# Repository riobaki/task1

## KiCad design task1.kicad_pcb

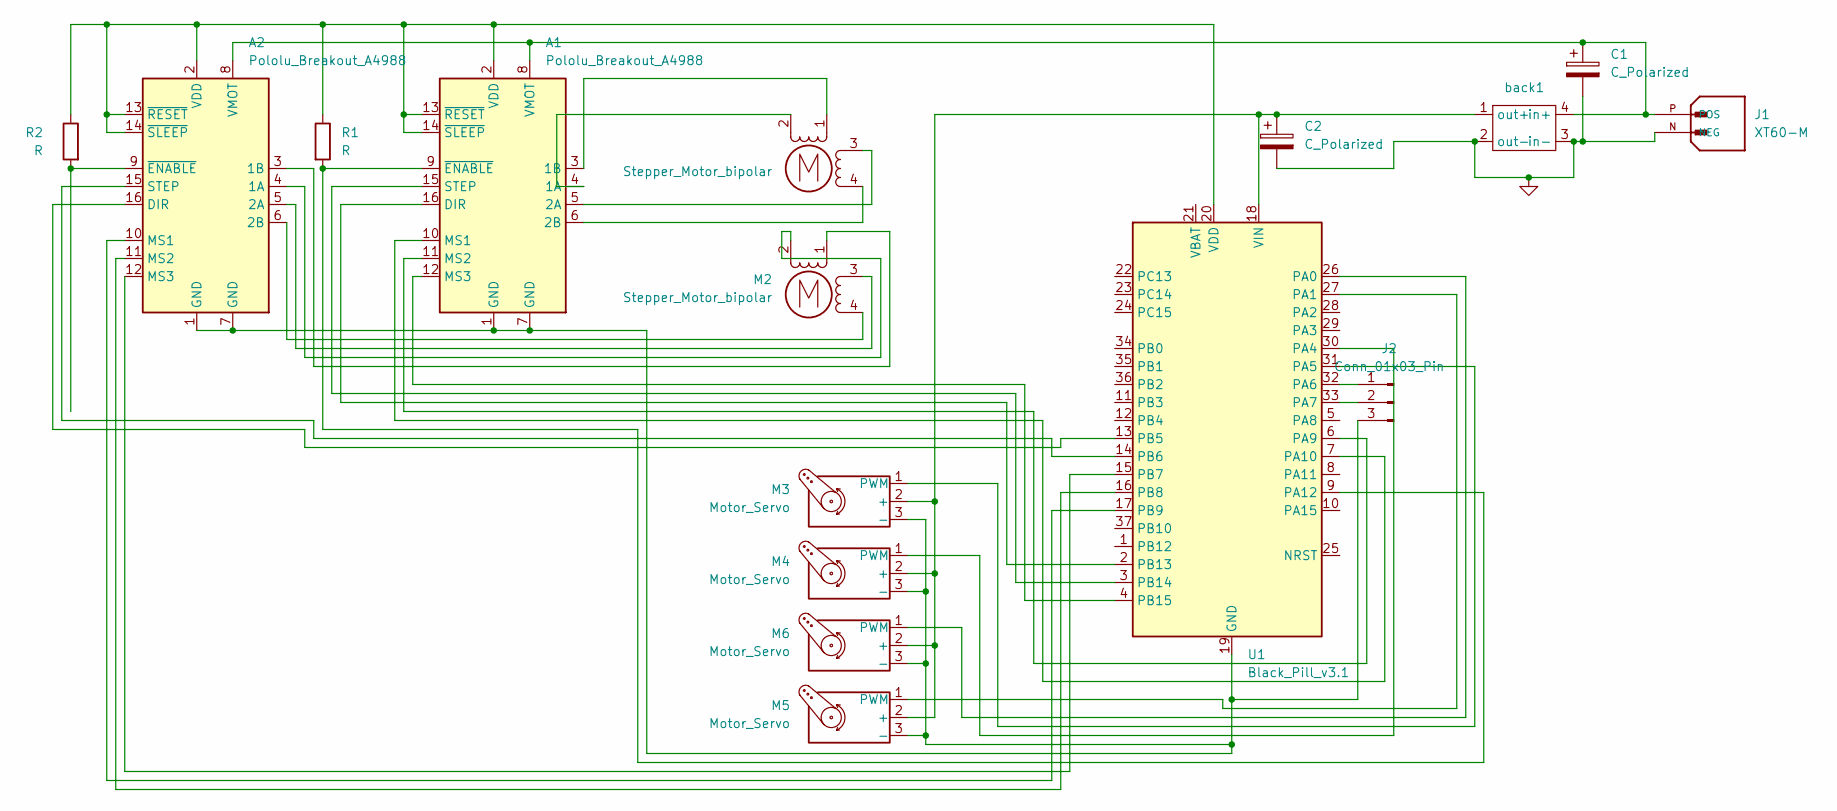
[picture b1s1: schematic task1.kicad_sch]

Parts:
A1, A2: Pololu_Breakout_A4988; Pololu_Breakout-16_15.2x20.3mm
C1, C2: C_Polarized; CP_Radial_D10.0mm_P7.50mm
J1: XT60-M; AMASS_XT60-M; PARTREV V1.2
J2: Conn_01x03_Pin; PinHeader_1x03_P2.54mm_Vertical
M2: Stepper_Motor_bipolar; PinHeader_1x04_P2.54mm_Vertical
M3, M4, M5, M6: Motor_Servo; PinHeader_1x03_P2.54mm_Vertical
MConnector_PinHeader_2.54mm:PinHeader_1x04_P2.54mm_Vertical1: Stepper_Motor_bipolar; PinHeader_1x04_P2.54mm_Vertical
R1, R2: R; R_Axial_DIN0204_L3.6mm_D1.6mm_P5.08mm_Horizontal
U1: Black_Pill_v3.1
back1: back

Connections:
unnamed: A1.4 (1A), MConnector_PinHeader_2.54mm:PinHeader_1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.2 (-_2)
unnamed: A1.3 (1B), MConnector_PinHeader_2.54mm:PinHeader_1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.1
unnamed: A1.5 (2A), MConnector_PinHeader_2.54mm:PinHeader_1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.3
unnamed: A1.6 (2B), MConnector_PinHeader_2.54mm:PinHeader_1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.4
unnamed: A1.16 (DIR), U1.2 (PB13)
unnamed: A1.10 (MS1), U1.7 (PA10)
unnamed: A1.11 (MS2), U1.6 (PA9)
unnamed: A1.12 (MS3), U1.4 (PB15)
unnamed: A1.15 (STEP), U1.3 (PB14)
unnamed: A1.8 (VMOT), A2.8 (VMOT), C1.1, J1.P (POS), back1.4 (in+)
unnamed: A1.9 (~ENABLE), R1.2, U1.9 (PA12)
unnamed: A2.4 (1A), M2.2 (-_2)
unnamed: A2.3 (1B), M2.1
unnamed: A2.5 (2A), M2.3
unnamed: A2.6 (2B), M2.4
unnamed: A2.16 (DIR), U1.13 (PB5)
unnamed: A2.10 (MS1), U1.17 (PB9)
unnamed: A2.11 (MS2), U1.16 (PB8)
unnamed: A2.12 (MS3), U1.15 (PB7)
unnamed: A2.15 (STEP), U1.14 (PB6)
unnamed: A2.9 (~ENABLE), R2.2
unnamed: J2.1, U1.32 (PA6)
unnamed: J2.2, U1.33 (PA7)
unnamed: M3.1 (PWM), U1.31 (PA5)
unnamed: M4.1 (PWM), U1.30 (PA4)
unnamed: M5.1 (PWM), U1.27 (PA1)
unnamed: M6.1 (PWM), U1.26 (PA0)
VDD: A1.2 (VDD), A1.13 (~RESET), A1.14 (~SLEEP), A2.2 (VDD), A2.13 (~RESET), A2.14 (~SLEEP), R1.1, R2.1, U1.20 (VDD), U1.38 (VDD)
VIN: C2.1, M3.2 (+), M4.2 (+), M5.2 (+), M6.2 (+), U1.18 (VIN), U1.40 (VIN), back1.1 (out+)

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
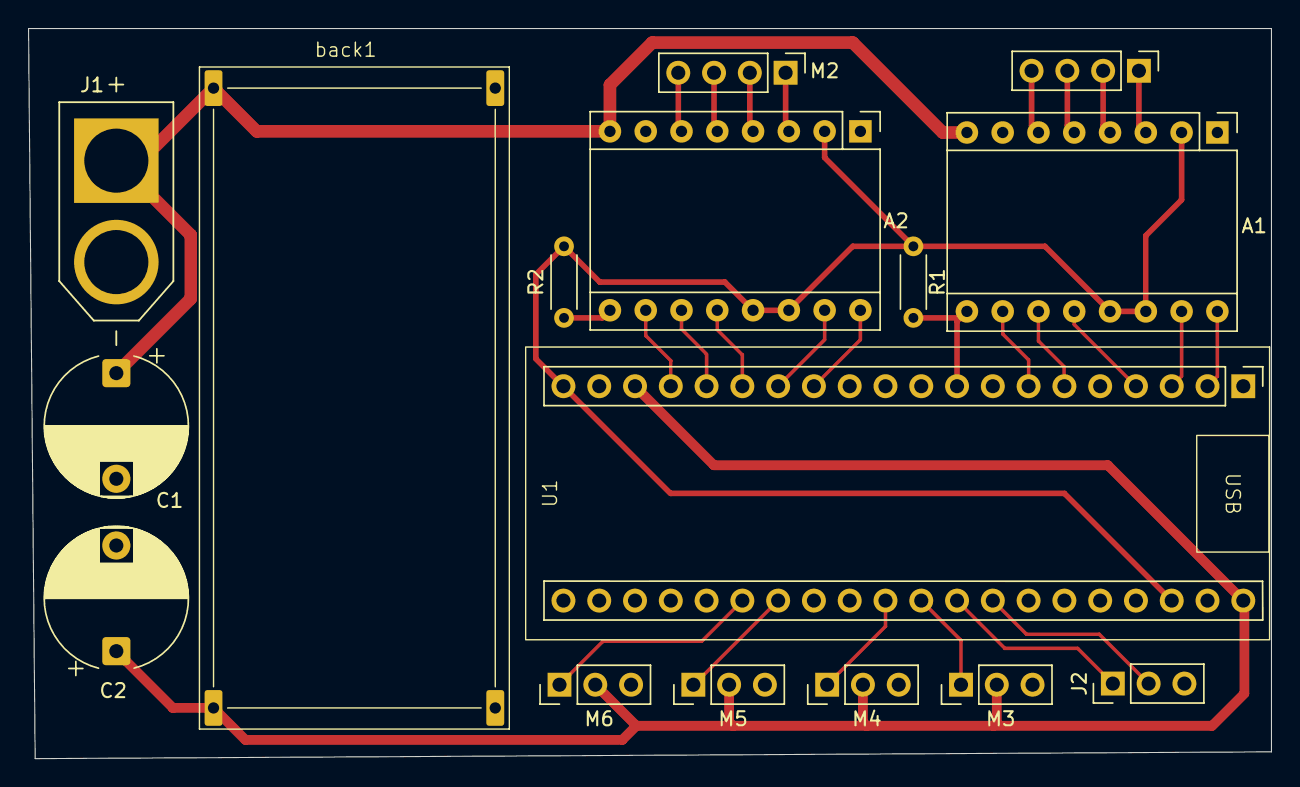
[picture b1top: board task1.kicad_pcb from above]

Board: 2 copper layers, 88.2 x 51.8 mm, 16 parts (0 on the bottom side), 30 nets.
